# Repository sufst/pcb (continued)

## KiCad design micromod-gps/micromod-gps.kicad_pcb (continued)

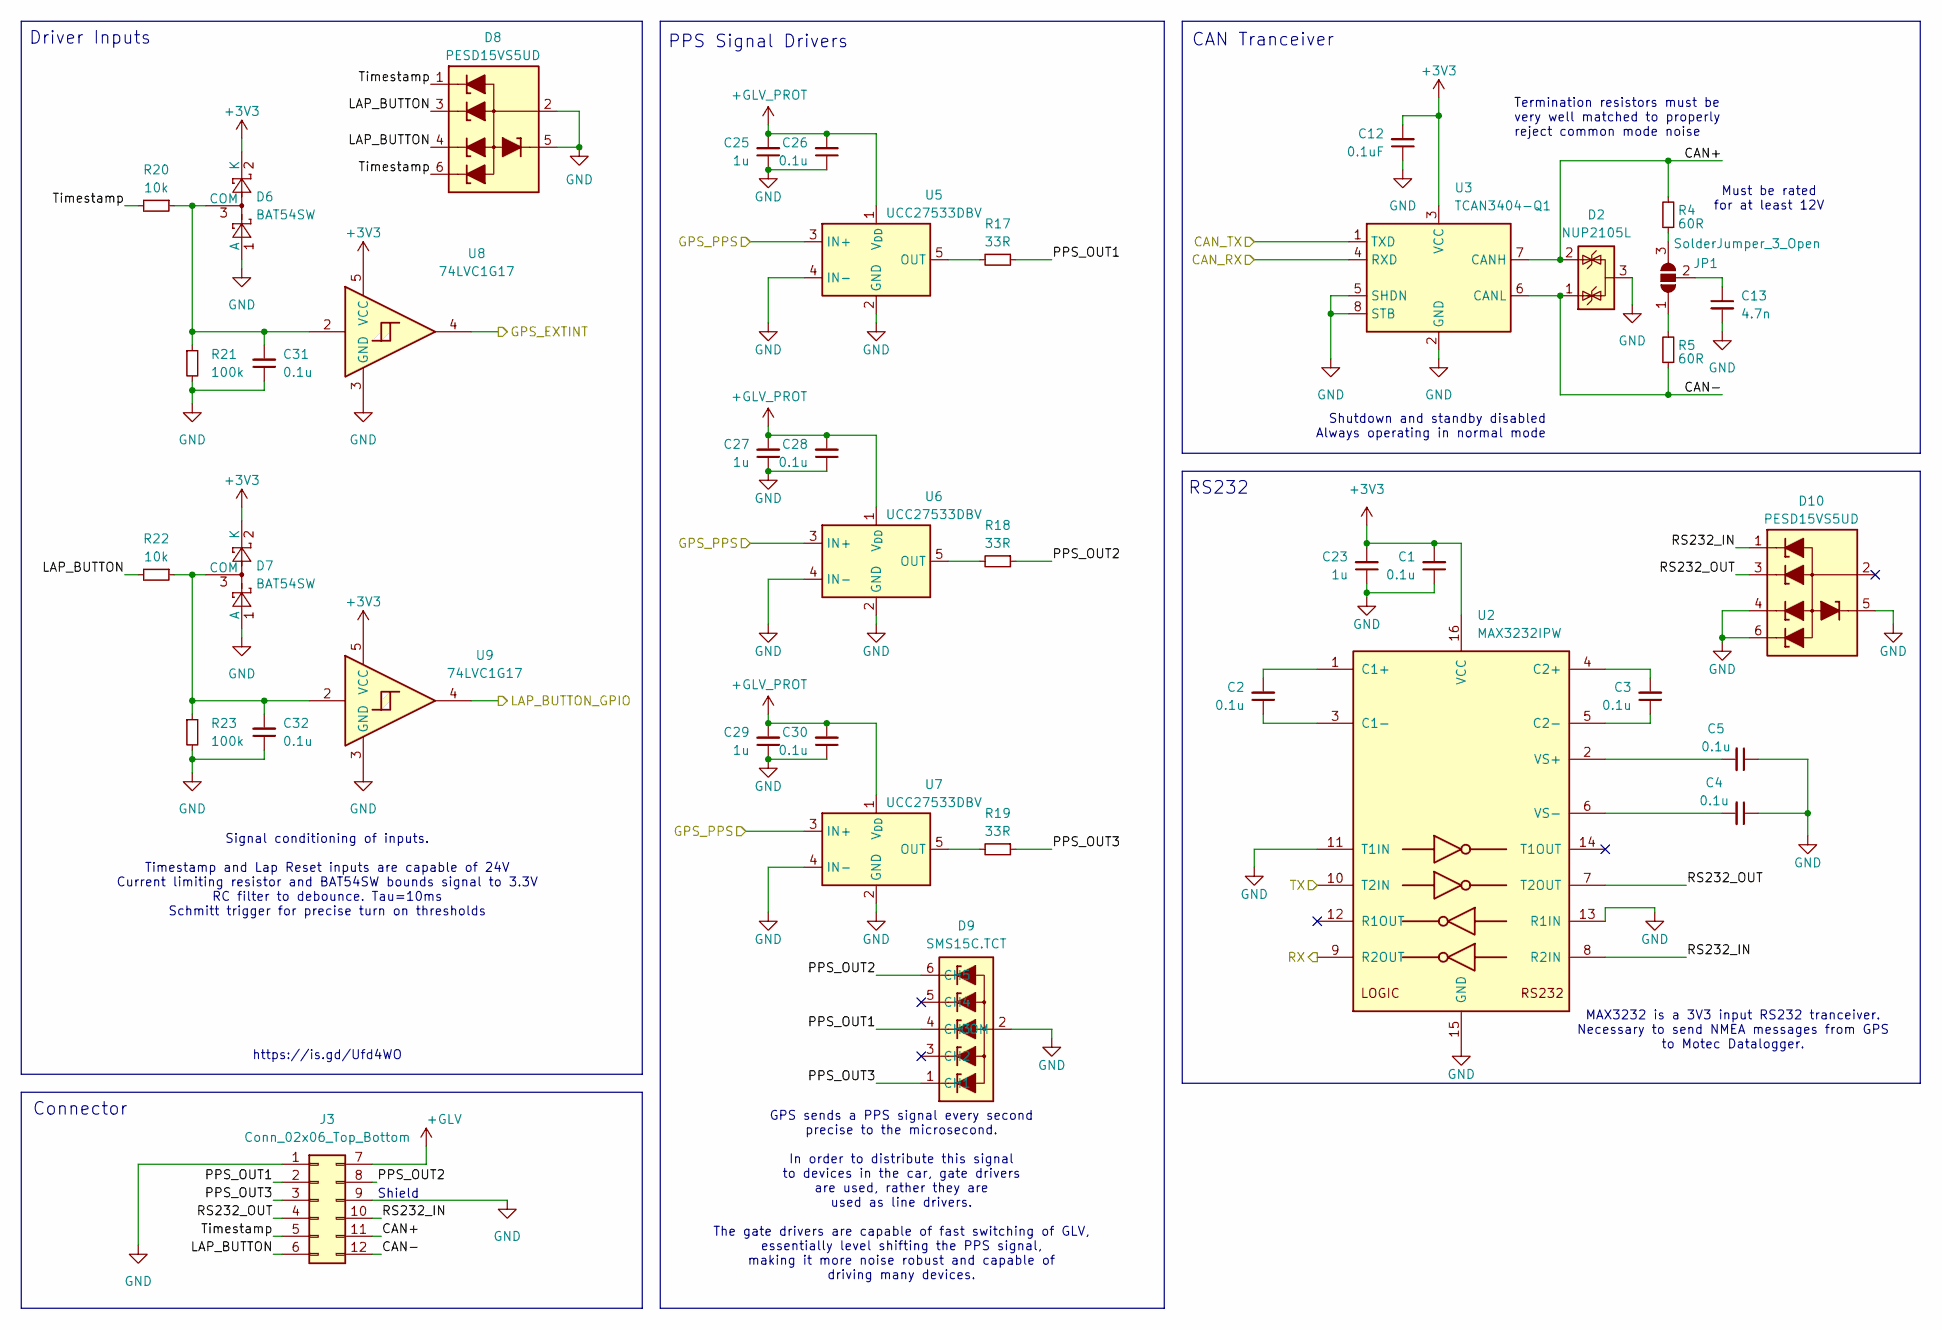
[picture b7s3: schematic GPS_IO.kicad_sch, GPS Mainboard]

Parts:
C1, C2, C3, C4, C5, C26, C28, C30, C31, C32: 0.1u; C_0603_1608Metric_Pad1.08x0.95mm_HandSolder; MPN CL10B104KB85PNL
C12: 0.1uF; C_0603_1608Metric_Pad1.08x0.95mm_HandSolder; MPN CL10B104KB85PNL
C13: 4.7n; C_0603_1608Metric_Pad1.08x0.95mm_HandSolder; MPN 885012206087
C23, C25, C27, C29: 1u; C_0603_1608Metric_Pad1.08x0.95mm_HandSolder; MPN UMK107BJ105KA-T
D2: NUP2105L; SOT-23; MPN NUP2105L
D6, D7: BAT54SW; SOT-323_SC-70_Handsoldering; MPN BAT54SW
D8, D10: PESD15VS5UD; SOT-23-6
D9: SMS15C.TCT; SOT-23-6; MPN SMS15C.TCT
J3: Conn_02x06_Top_Bottom; Molex_Micro-Fit_3.0_43045-1200_2x06_P3.00mm_Horizontal; MPN 43045-1200
JP1: SolderJumper_3_Open; SolderJumper-3_P1.3mm_Open_RoundedPad1.0x1.5mm
R4, R5: 60R; R_0603_1608Metric_Pad0.98x0.95mm_HandSolder; MPN RC0603FR-0760R4L
R17, R18, R19: 33R; R_0603_1608Metric_Pad0.98x0.95mm_HandSolder; MPN RT0603FRE0733RL
R20, R22: 10k; R_0603_1608Metric_Pad0.98x0.95mm_HandSolder; MPN RT0603RF1310KL
R21, R23: 100k; R_0603_1608Metric_Pad0.98x0.95mm_HandSolder; MPN RT0603FRE10100KL
U2: MAX3232IPW; TSSOP-16_4.4x5mm_P0.65mm; MPN MAX3232IPW
U3: TCAN3404-Q1; SOT-23-8_Handsoldering; MPN TCAN3404DDFRQ1
U5, U6, U7: UCC27533DBV; SOT-23-5_HandSoldering; MPN UCC27533DBV
U8, U9: 74LVC1G17; SOT-353_SC-70-5_Handsoldering; MPN 74LVC1G17

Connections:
+3V3: C1.2, C12.2, C23.2, D6.2 (K), D7.2 (K), U2.16 (VCC), U3.3 (VCC), U8.5 (VCC), U9.5 (VCC); also elsewhere on the board
+GLV: J3.7; also elsewhere on the board
+GLV_PROT: C25.2, C26.2, C27.2, C28.2, C29.2, C30.2, U5.1 (V_{DD}), U6.1 (V_{DD}), U7.1 (V_{DD}); also elsewhere on the board
/CAN_RX: U3.4 (RXD); also elsewhere on the board
/CAN_TX: U3.1 (TXD); also elsewhere on the board
/GPS_EXTINT: U8.4; also elsewhere on the board
/GPS_IO/CAN+: D2.2 (K), J3.11, R4.2, U3.7 (CANH)
/GPS_IO/CAN-: D2.1 (K), J3.12, R5.1, U3.6 (CANL)
/GPS_IO/LAP_BUTTON: D8.3 (L2), D8.4 (L3), J3.6, R22.2
/GPS_IO/PPS_OUT1: D9.4 (CH3), J3.2, R17.1
/GPS_IO/PPS_OUT2: D9.6 (CH5), J3.8, R18.1
/GPS_IO/PPS_OUT3: D9.1 (CH1), J3.3, R19.1
/GPS_IO/RS232_IN: D10.1 (L1), J3.10, U2.8 (R2IN)
/GPS_IO/RS232_OUT: D10.3 (L2), J3.4, U2.7 (T2OUT)
/GPS_IO/Timestamp: D8.1 (L1), D8.6 (L4), J3.5, R20.2
/GPS_PPS: U5.3 (IN+), U6.3 (IN+), U7.3 (IN+); also elsewhere on the board
/LAP_BUTTON: U9.4; also elsewhere on the board
/OFFBOARD_UART_IN: U2.9 (R2OUT); also elsewhere on the board
/OFFBOARD_UART_OUT: U2.10 (T2IN); also elsewhere on the board
GND: C1.1, C4.1, C5.1, C12.1, C13.2, C23.1, C25.1, C26.1, C27.1, C28.1, C29.1, C30.1, C31.1, C32.1, D2.3 (A), D6.1 (A), D7.1 (A), D8.2 (VN), D8.5 (VN), D9.2 (COM), D10.4 (L3), D10.5 (VN), D10.6 (L4), J3.1, J3.9, R21.2, R23.2, U2.11 (T1IN), U2.13 (R1IN), U2.15 (GND), U3.2 (GND), U3.5 (SHDN), U3.8 (STB), U5.2 (GND), U5.4 (IN-), U6.2 (GND), U6.4 (IN-), U7.2 (GND), U7.4 (IN-), U8.3 (GND), U9.3 (GND); also elsewhere on the board
unnamed: C31.2, D6.3 (COM), R20.1, R21.1, U8.2
unnamed: C32.2, D7.3 (COM), R22.1, R23.1, U9.2
unnamed: JP1.1 (A), R5.2
unnamed: JP1.3 (B), R4.1
unnamed: C13.1, JP1.2 (C)
unnamed: C2.2, U2.1 (C1+)
unnamed: C2.1, U2.3 (C1-)
unnamed: C3.2, U2.4 (C2+)
unnamed: C3.1, U2.5 (C2-)
unnamed: C5.2, U2.2 (VS+)
unnamed: C4.2, U2.6 (VS-)
unnamed: R17.2, U5.5 (OUT)
unnamed: R18.2, U6.5 (OUT)
unnamed: R19.2, U7.5 (OUT)

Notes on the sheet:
Driver Inputs
https://is.gd/Ufd4WO
Shutdown and standby disabled Always operating in normal mode
GPS sends a PPS signal every second precise to the microsecond. In order to distribute this signal to devices in the car, gate drivers are used, rather they are used as line drivers. The gate drivers are capable of fast switching of GLV, essentially level shifting the PPS signal, making it more noi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
Must be rated for at least 12V
Connector
RS232
MAX3232 is a 3V3 input RS232 tranceiver. Necessary to send NMEA messages from GPS to Motec Datalogger.
PPS Signal Drivers
Signal conditioning of inputs. Timestamp and Lap Reset inputs are capable of 24V Current limiting resistor and BAT54SW bounds signal to 3.3V RC filter to debounce. Tau=10ms Schmitt trigger for precise turn on thresholds
CAN Tranceiver
Shield
Termination resistors must be very well matched to properly reject common mode noise

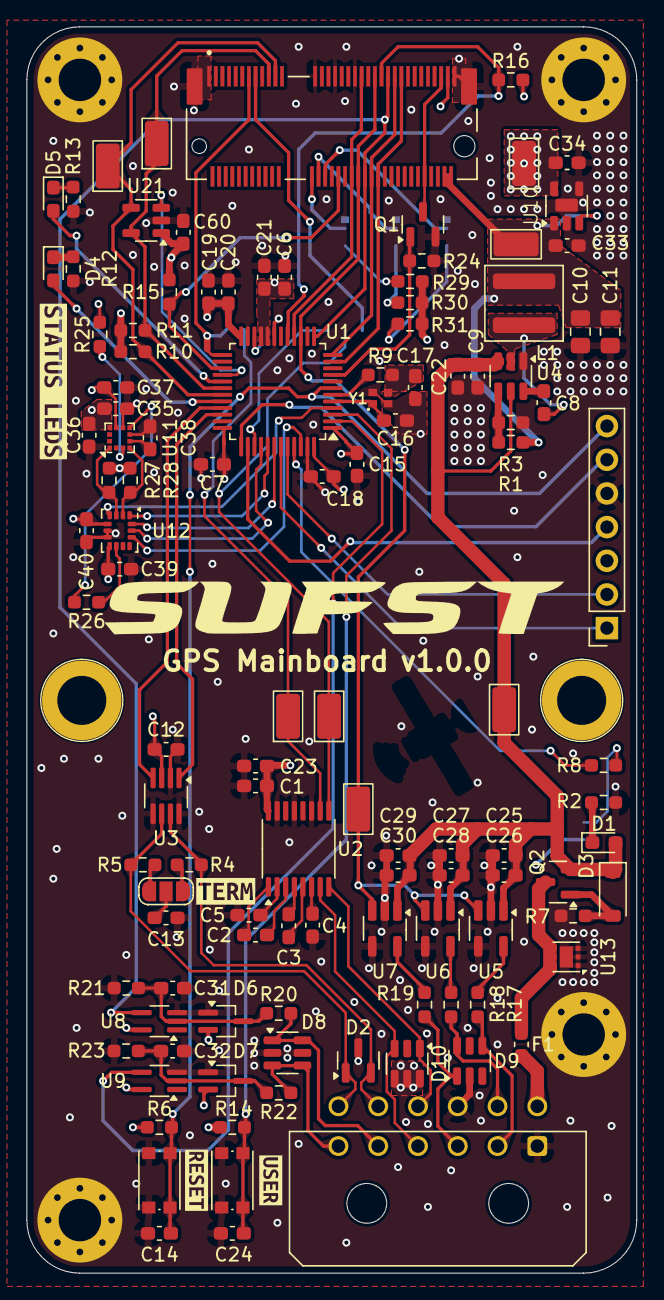
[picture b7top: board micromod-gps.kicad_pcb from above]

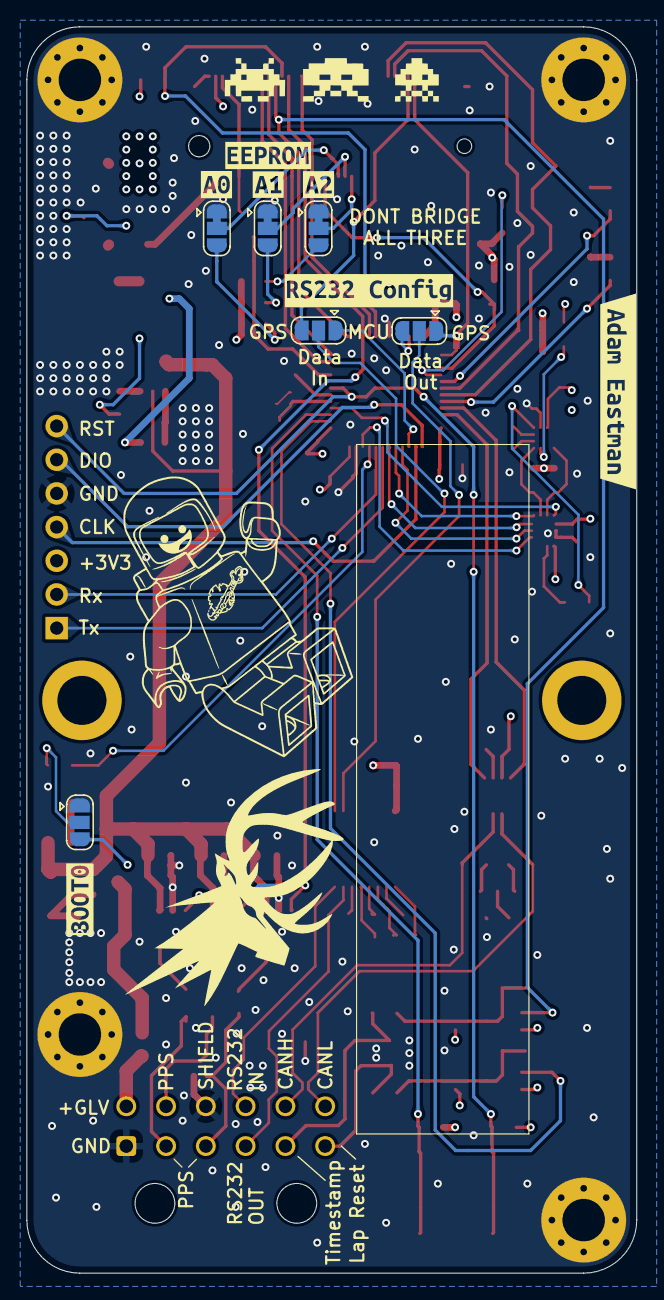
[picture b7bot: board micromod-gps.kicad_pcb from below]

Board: 4 copper layers, 46.0 x 94.0 mm, 139 parts (13 on the bottom side), 88 nets.

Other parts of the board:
kibuzzard-69CC78BA: G***; kibuzzard-69CC78BA
kibuzzard-69CC717E: G***; kibuzzard-69CC717E
kibuzzard-69CC718B: G***; kibuzzard-69CC718B
kibuzzard-69CC780C: G***; kibuzzard-69CC780C
kibuzzard-69CC784C: G***; kibuzzard-69CC784C
kibuzzard-69CC7130: G***; kibuzzard-69CC7130
kibuzzard-69CC7837: G***; kibuzzard-69CC7837
kibuzzard-69CC7843: G***; kibuzzard-69CC7843
kibuzzard-69CD1CA6: G***; kibuzzard-69CD1CA6
kibuzzard-69CD28D6: G***; kibuzzard-69CD28D6
kibuzzard-69D03494: G***; kibuzzard-69D03494

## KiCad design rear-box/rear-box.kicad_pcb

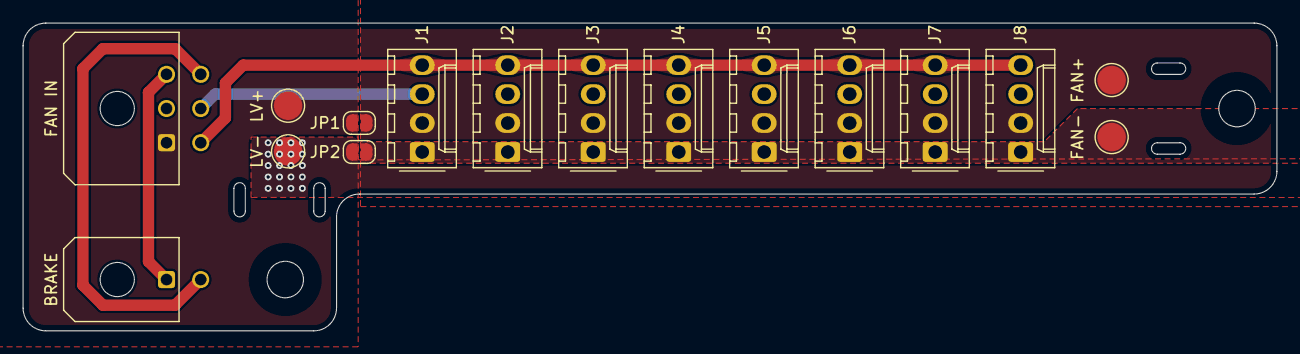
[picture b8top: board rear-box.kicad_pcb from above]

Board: 2 copper layers, 110.0 x 27.0 mm, 18 parts (0 on the bottom side), 8 nets.

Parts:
BRAKE: Molex 43045-0200; Molex_Micro-Fit_3.0_43045-0200_2x01_P3.00mm_Horizontal
FAN IN: Molex 43045-0600; Molex_Micro-Fit_3.0_43045-0600_2x03_P3.00mm_Horizontal
FAN+: Fan PWR+; TestPoint_Pad_D2.5mm
FAN-: Fan PWR-; TestPoint_Pad_D2.5mm
H1, H2: MountingHole; MountingHole_3.2mm_M3_DIN965
J1, J2, J3, J4, J5, J6, J7, J8: Molex KK 254; Molex_KK-254_AE-6410-04A_1x04_P2.54mm_Vertical
JP1, JP2: Power Select; SolderJumper-2_P1.3mm_Open_RoundedPad1.0x1.5mm
LV+: FAN_EXC; TestPoint_Pad_D2.5mm
LV-: LV_GND; TestPoint_Pad_D2.5mm

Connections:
+12V: FAN IN.1, JP1.1 (A), LV+.1
+VDC: FAN+.1, J1.2, J2.2, J3.2, J4.2, J5.2, J6.2, J7.2, J8.2, JP1.2 (B)
/BRK+: BRAKE.1, FAN IN.3
/BRK-: BRAKE.2, FAN IN.6
/PWM: FAN IN.4, J1.4, J2.4, J3.4, J4.4, J5.4, J6.4, J7.4, J8.4
/TACH: FAN IN.5, J1.3
GND: FAN IN.2, JP2.1 (A), LV-.1
PGND: FAN-.1, J1.1, J2.1, J3.1, J4.1, J5.1, J6.1, J7.1, J8.1, JP2.2 (B)
